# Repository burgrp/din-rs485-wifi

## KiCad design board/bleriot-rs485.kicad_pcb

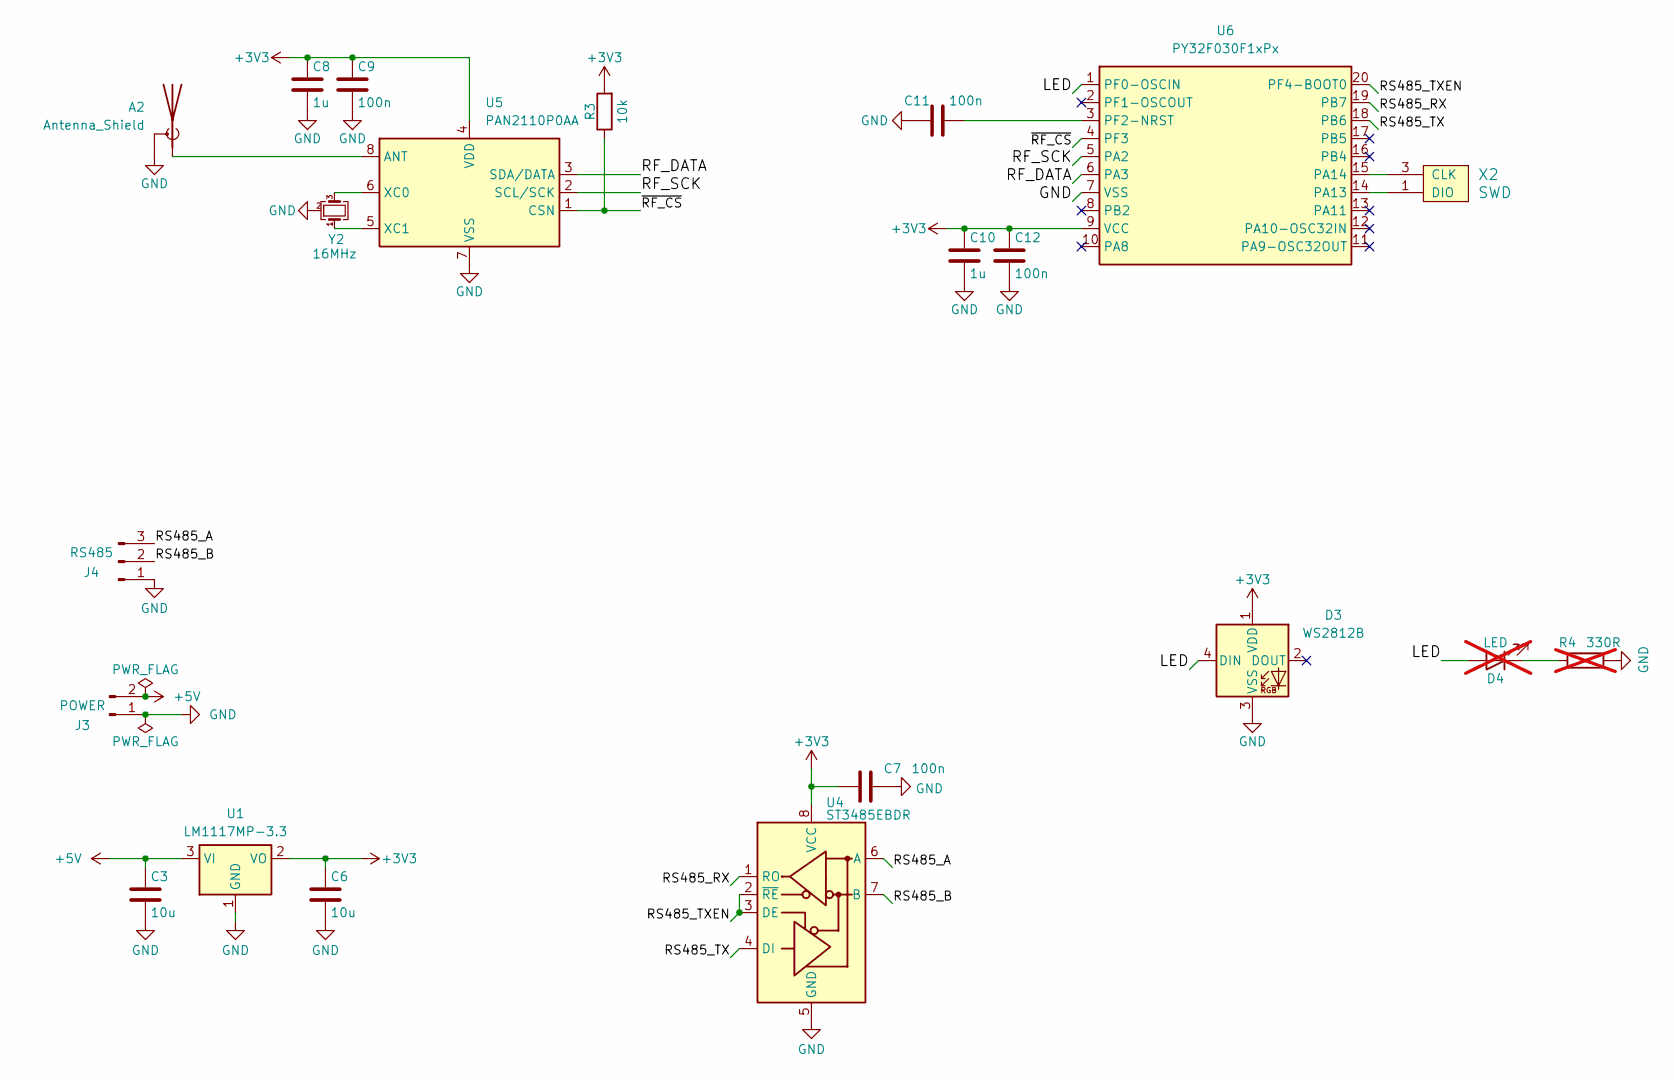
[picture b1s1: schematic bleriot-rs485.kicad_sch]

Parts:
A2: Antenna_Shield; Texas_SWRA117D_2.4GHz_Right
C3, C6: 10u; C_0805_2012Metric
C7, C9, C11, C12: 100n; C_0805_2012Metric
C8, C10: 1u; C_0805_2012Metric
D3: WS2812B; LED_WS2812B_PLCC4_5.0x5.0mm_P3.2mm
D4: LED; LED_0805_2012Metric_Pad1.15x1.40mm_HandSolder; not fitted
J3: POWER; PhoenixContact_MC_1,5_2-G-3.5_1x02_P3.50mm_Horizontal
J4: RS485; PhoenixContact_MC_1,5_3-G-3.5_1x03_P3.50mm_Horizontal
R3: 10k; R_0805_2012Metric
R4: 330R; R_0805_2012Metric; not fitted
U1: LM1117MP-3.3; SOT-223-3_TabPin2
U4: ST3485EBDR; SOIC-8_3.9x4.9mm_P1.27mm
U5: PAN2110P0AA; SOIC-8_3.9x4.9mm_P1.27mm
U6: PY32F030F1xPx; TSSOP-20_4.4x6.5mm_P0.65mm
X2: SWD
Y2: 16MHz; Crystal_SMD_3225-4Pin_3.2x2.5mm

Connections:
+3V3: C6.1, C7.1, C8.1, C9.1, C10.1, C12.1, D3.1 (VDD), R3.2, U1.2 (VO), U4.8 (VCC), U5.4 (VDD), U6.9 (VCC)
+5V: C3.1, J3.2, U1.3 (VI)
/LED: D3.4 (DIN), D4.2 (A), U6.1 (PF0-OSCIN)
/RF_DATA: U5.3 (SDA/DATA), U6.6 (PA3)
/RF_SCK: U5.2 (SCL/SCK), U6.5 (PA2)
/RS485_A: J4.3, U4.6 (A)
/RS485_B: J4.2, U4.7 (B)
/RS485_RX: U4.1 (RO), U6.19 (PB7)
/RS485_TX: U4.4 (DI), U6.18 (PB6)
/RS485_TXEN: U4.2 (~RE), U4.3 (DE), U6.20 (PF4-BOOT0)
/~RF_CS: R3.1, U5.1 (CSN), U6.4 (PF3)
GND: A2.2 (Shield), C3.2, C6.2, C7.2, C8.2, C9.2, C10.2, C11.2, C12.2, D3.3 (VSS), J3.1, J4.1, R4.1, U1.1 (GND), U4.5 (GND), U5.7 (VSS), U6.7 (VSS), X2.2 (GND), Y2.2 (G), Y2.4 (G)
unnamed: A2.1 (A), U5.8 (ANT)
unnamed: D4.1 (K), R4.2
unnamed: U5.6 (XC0), Y2.3
unnamed: U5.5 (XC1), Y2.1
unnamed: U6.14 (PA13), X2.1 (DIO)
unnamed: U6.15 (PA14), X2.3 (CLK)
unnamed: C11.1, U6.3 (PF2-NRST)

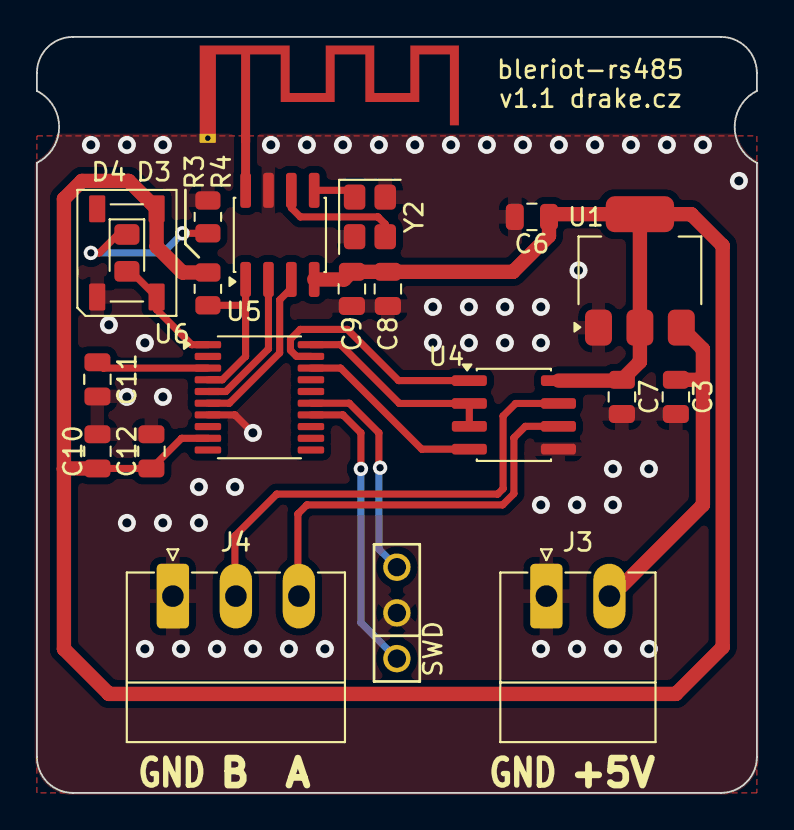
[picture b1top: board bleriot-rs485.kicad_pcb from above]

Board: 2 copper layers, 40.0 x 42.0 mm, 21 parts (0 on the bottom side), 19 nets.

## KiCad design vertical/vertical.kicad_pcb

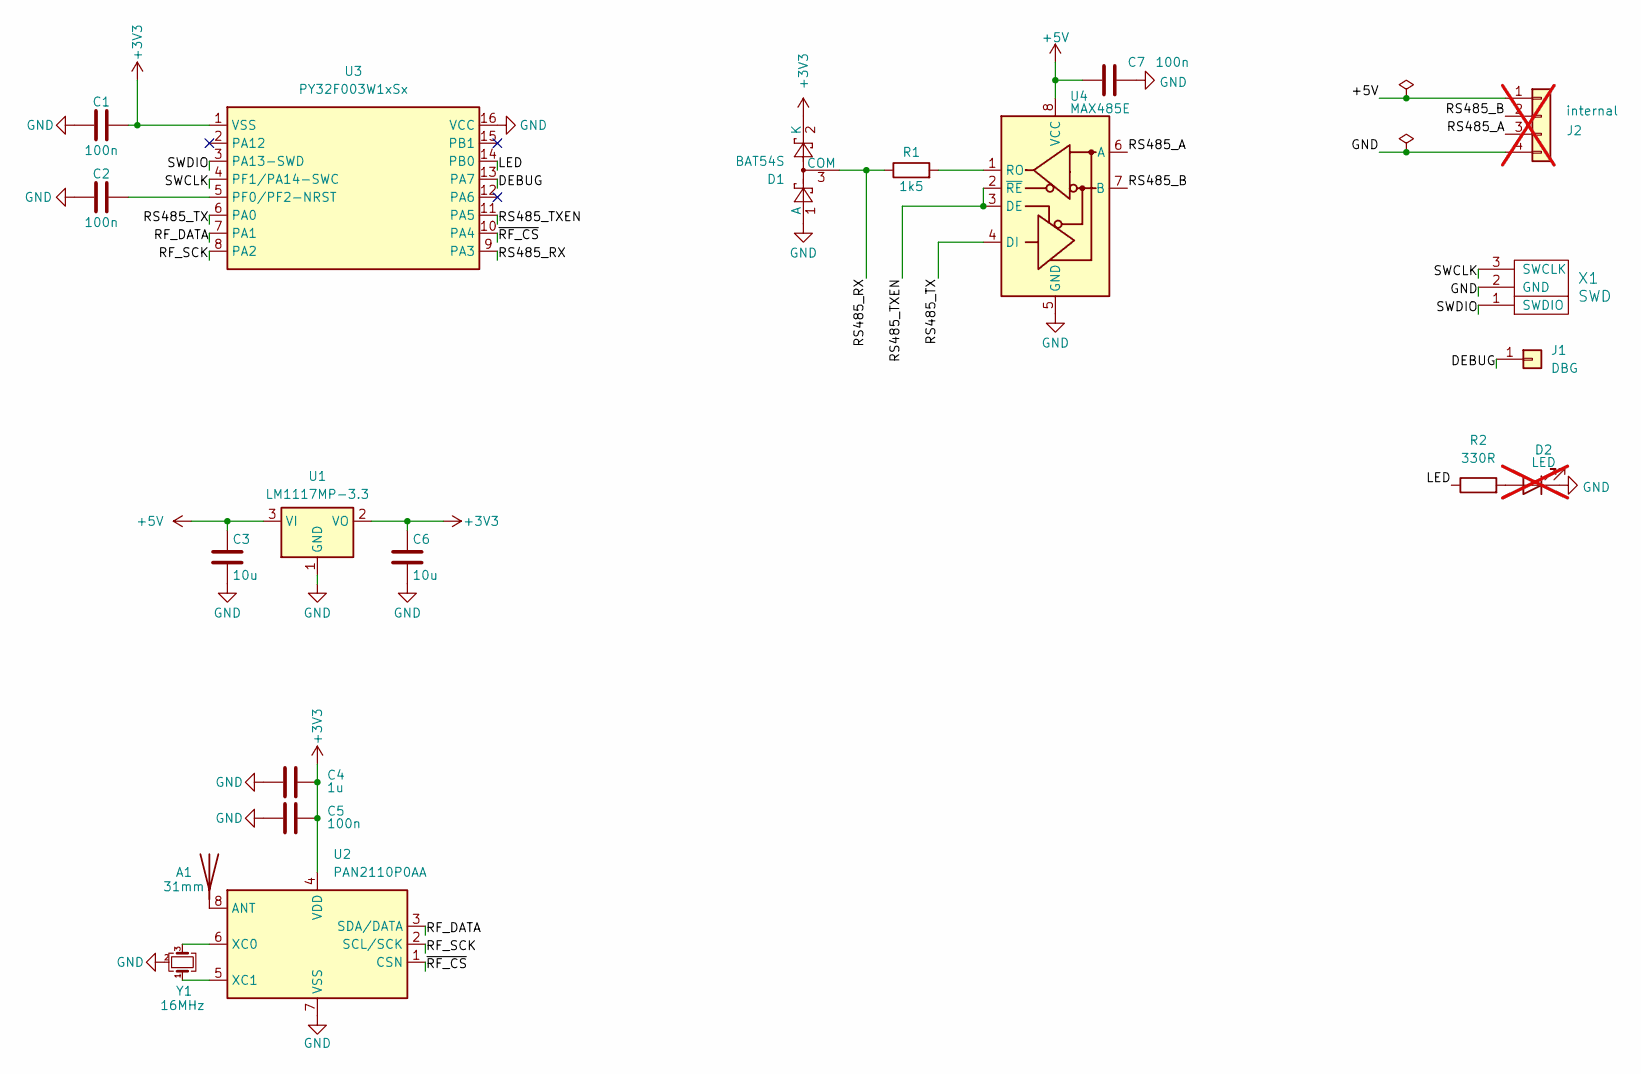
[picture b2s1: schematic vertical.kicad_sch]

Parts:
A1: 31mm; Wire antena 2.4GHz
C1, C2, C5, C7: 100n; C_0805_2012Metric
C3, C6: 10u; C_0805_2012Metric
C4: 1u; C_0805_2012Metric
D1: BAT54S; SOT-23
D2: LED; LED_2010_5025Metric; not fitted
J1: DBG; PinHeader_1x01_P2.54mm_Vertical
J2: internal; PinHeader_1x04_P2.54mm_Horizontal; not fitted
R1: 1k5; R_0805_2012Metric
R2: 330R; R_0805_2012Metric
U1: LM1117MP-3.3; SOT-223-3_TabPin2
U2: PAN2110P0AA; SOIC-8_3.9x4.9mm_P1.27mm
U3: PY32F003W1xSx; SOIC-16_3.9x9.9mm_P1.27mm
U4: MAX485E; SOIC-8_3.9x4.9mm_P1.27mm
X1: SWD
Y1: 16MHz; Crystal_SMD_3225-4Pin_3.2x2.5mm

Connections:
+3V3: C1.1, C4.1, C5.1, C6.1, D1.2 (K), U1.2 (VO), U2.4 (VDD), U3.1 (VSS)
+5V: C3.1, C7.1, J2.1, U1.3 (VI), U4.8 (VCC)
/DEBUG: J1.1, U3.13 (PA7)
/LED: R2.1, U3.14 (PB0)
/RF_DATA: U2.3 (SDA/DATA), U3.7 (PA1)
/RF_SCK: U2.2 (SCL/SCK), U3.8 (PA2)
/RS485_A: J2.3, U4.6 (A)
/RS485_B: J2.2, U4.7 (B)
/RS485_RX: D1.3 (COM), R1.1, U3.9 (PA3)
/RS485_TX: U3.6 (PA0), U4.4 (DI)
/RS485_TXEN: U3.11 (PA5), U4.2 (~RE), U4.3 (DE)
/SWCLK: U3.4 (PF1/PA14-SWC), X1.3 (SWCLK)
/SWDIO: U3.3 (PA13-SWD), X1.1 (SWDIO)
/~RF_CS: U2.1 (CSN), U3.10 (PA4)
GND: C1.2, C2.2, C3.2, C4.2, C5.2, C6.2, C7.2, D1.1 (A), D2.1 (K), J2.4, U1.1 (GND), U2.7 (VSS), U3.16 (VCC), U4.5 (GND), X1.2 (GND), Y1.2 (G), Y1.4 (G)
unnamed: A1.1 (A), U2.8 (ANT)
unnamed: D2.2 (A), R2.2
unnamed: U2.6 (XC0), Y1.3
unnamed: U2.5 (XC1), Y1.1
unnamed: C2.1, U3.5 (PF0/PF2-NRST)
unnamed: R1.2, U4.1 (RO)

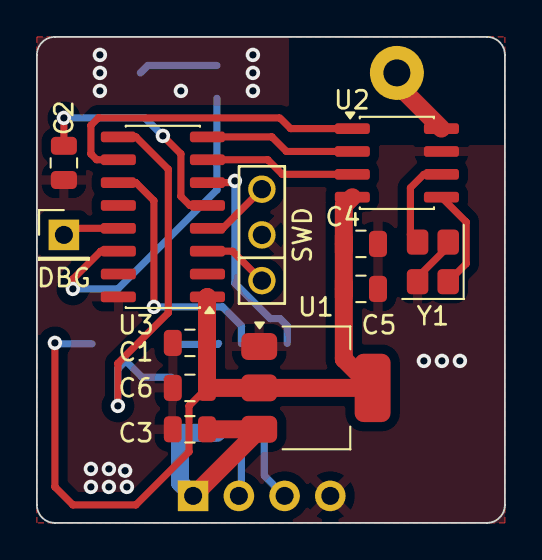
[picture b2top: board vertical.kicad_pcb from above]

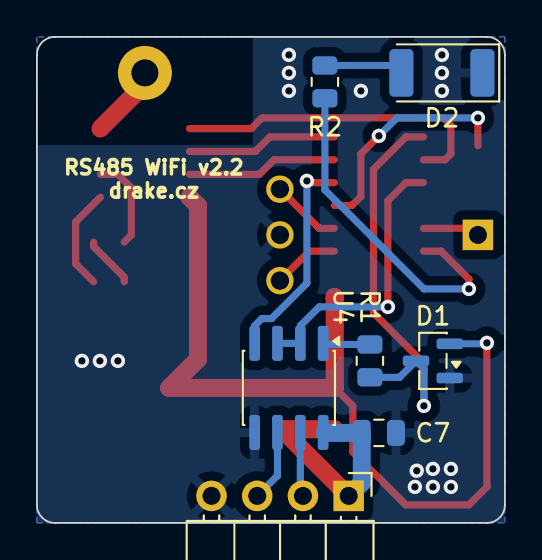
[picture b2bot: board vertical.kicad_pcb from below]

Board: 2 copper layers, 26.0 x 27.0 mm, 20 parts (7 on the bottom side), 21 nets.

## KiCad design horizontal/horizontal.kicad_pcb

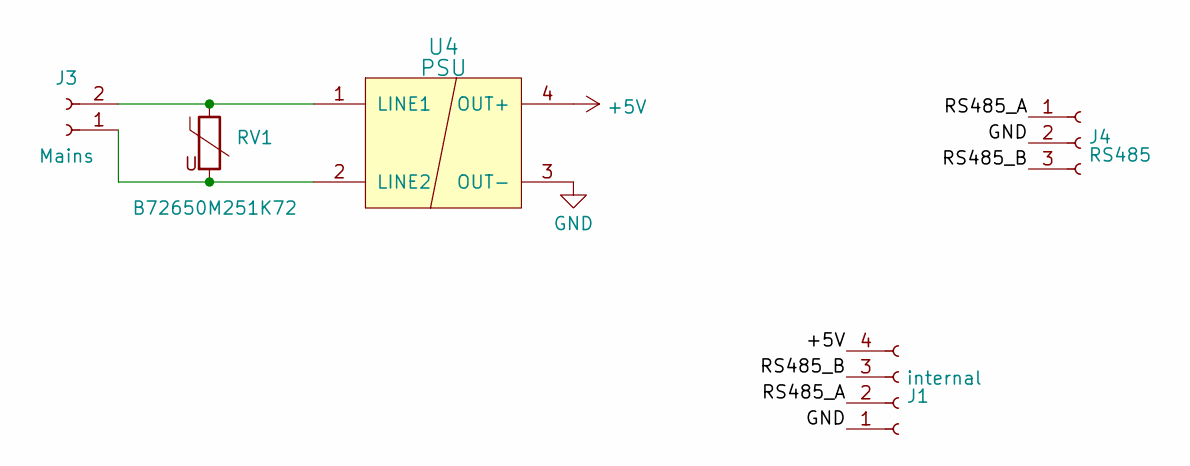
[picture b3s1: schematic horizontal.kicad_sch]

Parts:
J1: internal; PinSocket_1x04_P2.54mm_Vertical
J3: Mains; DG235-3.81-02P
J4: RS485; DG235-3.81-03P
RV1: B72650M251K72; R_1210_3225Metric_Pad1.30x2.65mm_HandSolder
U4: PSU; RQG 5V-0.6A-vertical

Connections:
+5V: J1.4, U4.4 (OUT+)
/RS485_A: J1.2, J4.1
/RS485_B: J1.3, J4.3
GND: J1.1, J4.2, U4.3 (OUT-)
unnamed: J3.1, RV1.2, U4.2 (LINE2)
unnamed: J3.2, RV1.1, U4.1 (LINE1)

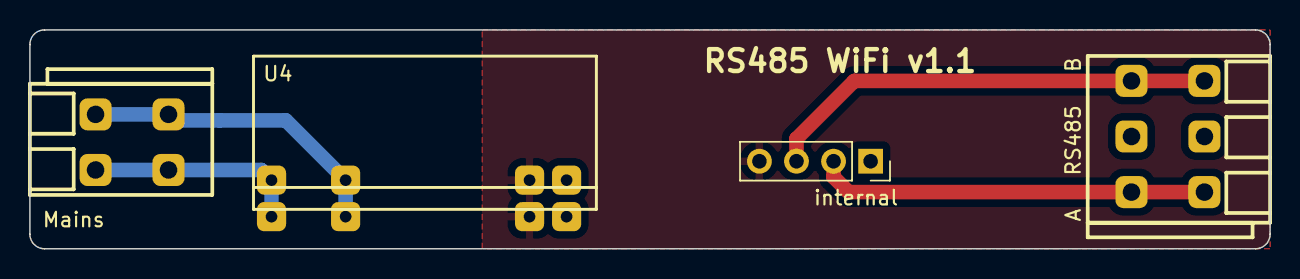
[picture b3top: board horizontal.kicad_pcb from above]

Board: 2 copper layers, 85.0 x 15.0 mm, 5 parts (1 on the bottom side), 6 nets.

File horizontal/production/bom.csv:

Designator,Footprint,Quantity,Value,LCSC Part #
J1,PinSocket_1x04_P2.54mm_Vertical,1,internal,
J3,DG235-3.81-02P,1,Mains,
J4,DG235-3.81-03P,1,RS485,
RV1,R_1210_3225Metric_Pad1.30x2.65mm_HandSolder,1,B72650M251K72,
U4,RQG 5V-0.6A-vertical,1,PSU,

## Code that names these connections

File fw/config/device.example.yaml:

device_type: din.rs485.energy.v1

node:
  uid: "0x0102030405060708"
  xtea_key: "00112233445566778899aabbccddeeff"
  pins:
    rs485_tx: PA0
    rs485_rx: PA3
    rs485_txen: PA5
    led: PB0
    rf_data: PA1
    rf_sck: PA2
    rf_cs: PA4
    debug: PA7
  poll_ms: 1000
  read_retries: 5

devices:
  - name: em.grid
    slave_addr: 1
    baud: 9600
    model: sinotimer_3p
  - name: em.house
    slave_addr: 2
    baud: 9600
    model: sinotimer_3p

register_map:
  - tag: 0x1000
    name: voltage.1
    title: Voltage L1
    unit: V
    address: 0x0000
    scale_milli: 1000
  - tag: 0x1001
    name: voltage.2
    title: Voltage L2
    unit: V
    address: 0x0002
    scale_milli: 1000
  - tag: 0x1002
    name: voltage.3
    title: Voltage L3
    unit: V
    address: 0x0004
    scale_milli: 1000

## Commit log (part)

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2023-07-08 feat: add reviewpad.yml file
2023-07-14 test commit
2024-11-12 retry, builder upgrade
2024-11-14 board update
2024-11-14 Refactor ModbusRegister class and update registry initialization
2025-01-20 rewrite in progress
2025-05-23 Update UART timeout character for improved communication stability
2026-06-17 Update KiCad design files
